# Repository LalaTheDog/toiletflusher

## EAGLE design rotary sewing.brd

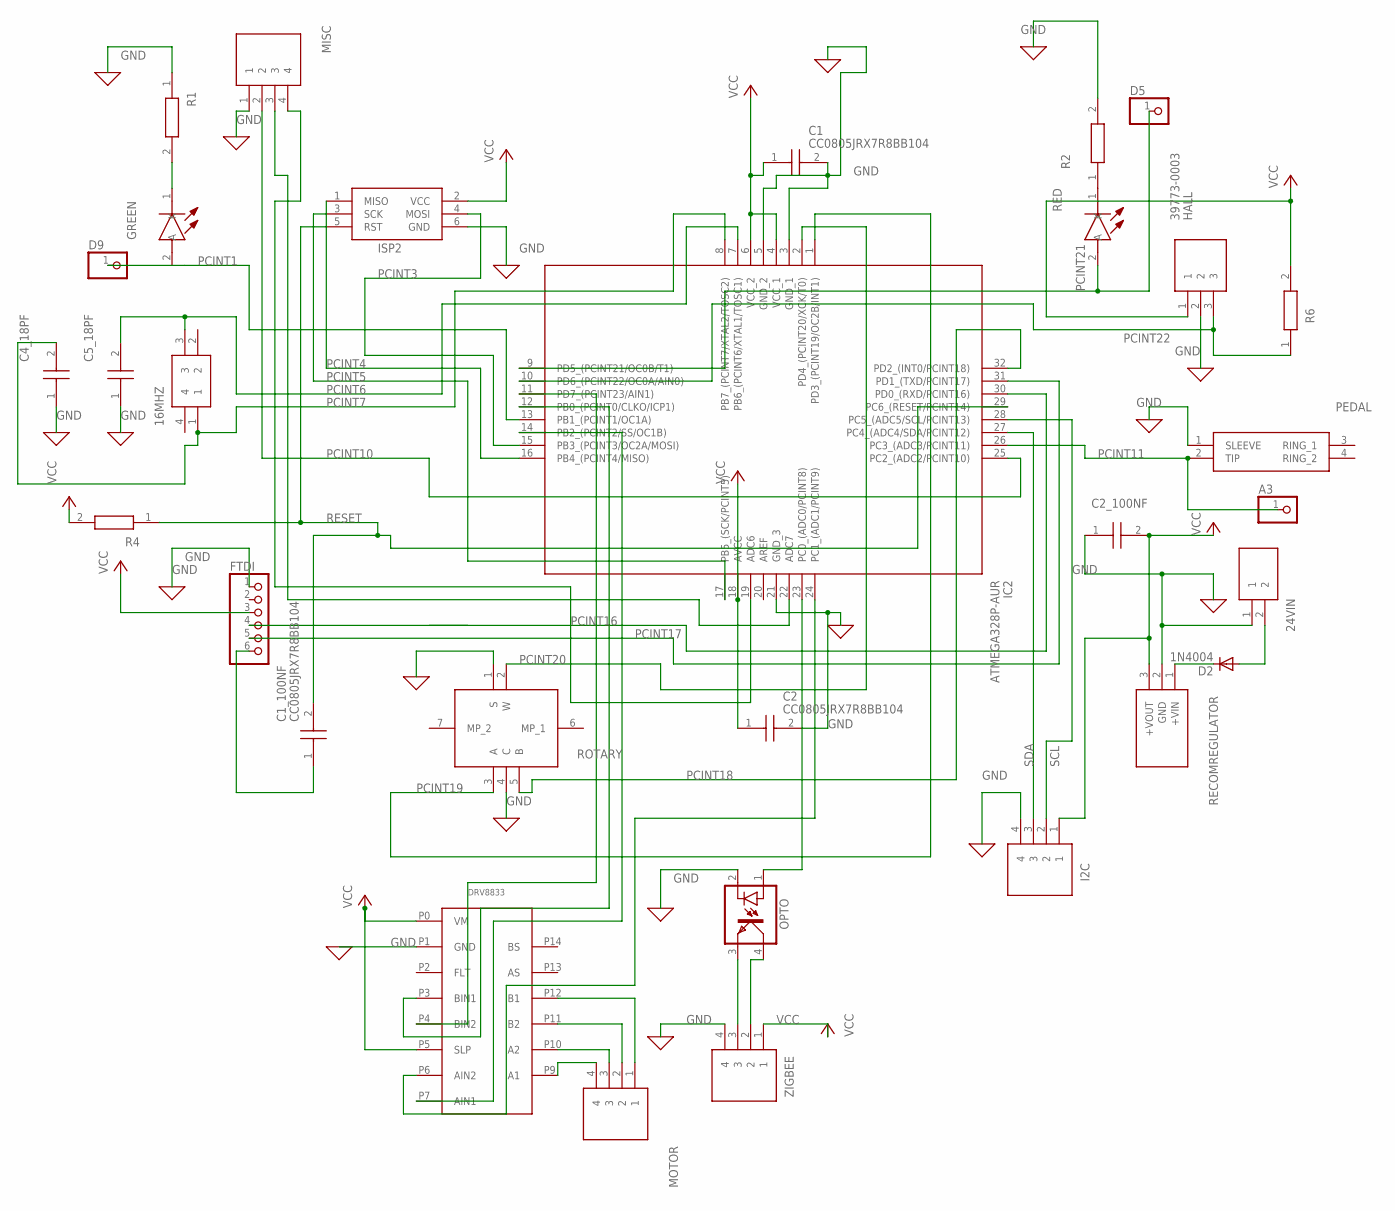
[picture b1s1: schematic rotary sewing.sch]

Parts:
16MHZ: 403C11E16M00000; 403C1XA32M00000
24VIN: 39773-0002; SHDR2W110P0X254_1X2_554X650X10
A3: PINHD-1X1; 1X01
C1, C1_100NF, C2, C2_100NF: CC0805JRX7R8BB104; CAPC2012X135N
C4_18PF, C5_18PF: C0805C180J5GACTU; CAPC2012X88N
D2: 1N4004; DO41-10
D5, D9: PINHD-1X1; 1X01
DRV8833: DRV8833
FTDI: PINHD-1X6; 1X06
GREEN: LTST-C171GKT; LEDC2012X90N
HALL: 39773-0003; SHDR3W80P0X254_1X3_808X650X101
I2C: 39773-0004; SHDR4W80P0X254_1X4_1062X650X10
IC2: ATMEGA328P-AUR; QFP80P900X900X120-32N
ISP2: AVRISP-6; AVRISP
MISC: 39773-0004; SHDR4W80P0X254_1X4_1062X650X10
MOTOR: 39773-0004; SHDR4W80P0X254_1X4_1062X650X10
OPTO: PC817; DIL04
PEDAL: SJ2-3574A-SMT-TR; SJ23574ASMTTR
R1, R2: RMC1_10K1001FTP; RESC2012X65N
R4, R6: ERA-6AED103V; RESC2012X60N
RECOMREGULATOR: R-78E3.3-1.0
RED: LTST-C171KRKT; LEDM2012X90N
ROTARY: PEC11L-4220F-S0015; PEC11L4220FS0015
ZIGBEE: 39773-0004; SHDR4W80P0X254_1X4_1062X650X10

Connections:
GND: 24VIN.1, C1.2, C2.2, C2_100NF.1, C4_18PF.1, C5_18PF.1, DRV8833.P1 (GND), FTDI.1, HALL.2, I2C.4, IC2.3 (GND_1), IC2.5 (GND_2), IC2.21 (GND_3), ISP2.6 (GND), MISC.1, OPTO.2 (C), PEDAL.1 (SLEEVE), R1.1, R2.2, RECOMREGULATOR.2 (GND), ROTARY.1 (S), ROTARY.4 (C), ZIGBEE.4
unnamed: OPTO.3 (EMIT), ZIGBEE.3
unnamed: IC2.23 (PC0_(ADC0/PCINT8)), OPTO.1 (A)
unnamed: OPTO.4 (COL), ZIGBEE.2
unnamed: 24VIN.2, D2.A
unnamed: R2.1, RED.1 (K)
unnamed: GREEN.1 (K), R1.2
unnamed: DRV8833.P9 (A1), MOTOR.4
unnamed: DRV8833.P10 (A2), MOTOR.3
unnamed: DRV8833.P11 (B2), MOTOR.2
unnamed: DRV8833.P12 (B1), MOTOR.1
unnamed: C1_100NF.1, FTDI.6
unnamed: DRV8833.P4 (BIN2), IC2.11 (PD7_(PCINT23/AIN1))
unnamed: D2.C, RECOMREGULATOR.1 (+VIN)
unnamed: DRV8833.P3 (BIN1), IC2.12 (PB0_(PCINT0/CLKO/ICP1))
unnamed: DRV8833.P7 (AIN1), IC2.14 (PB2_(PCINT2/SS/OC1B))
unnamed: DRV8833.P6 (AIN2), IC2.24 (PC1_(ADC1/PCINT9))
unnamed: IC2.22 (ADC7), MISC.3
unnamed: IC2.19 (ADC6), MISC.4
PCINT1: D9.1, GREEN.2 (A), IC2.13 (PB1_(PCINT1/OC1A))
PCINT3: IC2.15 (PB3_(PCINT3/OC2A/MOSI)), ISP2.4 (MOSI)
PCINT4: IC2.16 (PB4_(PCINT4/MISO)), ISP2.1 (MISO)
PCINT5: IC2.17 (PB5_(SCK/PCINT5)), ISP2.3 (SCK)
PCINT6: 16MHZ.3, C5_18PF.2, IC2.7 (PB6_(PCINT6/XTAL1/TOSC1))
PCINT7: 16MHZ.1, C4_18PF.2, IC2.8 (PB7_(PCINT7/XTAL2/TOSC2))
PCINT10: IC2.25 (PC2_(ADC2/PCINT10)), MISC.2
PCINT11: A3.1, IC2.26 (PC3_(ADC3/PCINT11)), PEDAL.2 (TIP)
PCINT16: FTDI.4, IC2.30 (PD0_(RXD/PCINT16))
PCINT17: FTDI.5, IC2.31 (PD1_(TXD/PCINT17))
PCINT18: IC2.32 (PD2_(INT0/PCINT18)), ROTARY.5 (B)
PCINT19: IC2.1 (PD3_(PCINT19/OC2B/INT1)), ROTARY.3 (A)
PCINT20: IC2.2 (PD4_(PCINT20/XCK/T0)), ROTARY.2 (W)
PCINT21: D5.1, IC2.9 (PD5_(PCINT21/OC0B/T1)), RED.2 (A)
PCINT22: HALL.3, IC2.10 (PD6_(PCINT22/OC0A/AIN0)), R6.1
RESET: C1_100NF.2, IC2.29 (PC6_(RESET/PCINT14)), ISP2.5 (RST), R4.1
SCL: I2C.2, IC2.28 (PC5_(ADC5/SCL/PCINT13))
SDA: I2C.3, IC2.27 (PC4_(ADC4/SDA/PCINT12))
VCC: C1.1, C2.1, C2_100NF.2, DRV8833.P0 (VM), DRV8833.P5 (SLP), FTDI.3, HALL.1, I2C.1, IC2.4 (VCC_1), IC2.6 (VCC_2), IC2.18 (AVCC), ISP2.2 (VCC), R4.2, R6.2, RECOMREGULATOR.3 (+VOUT), ZIGBEE.1

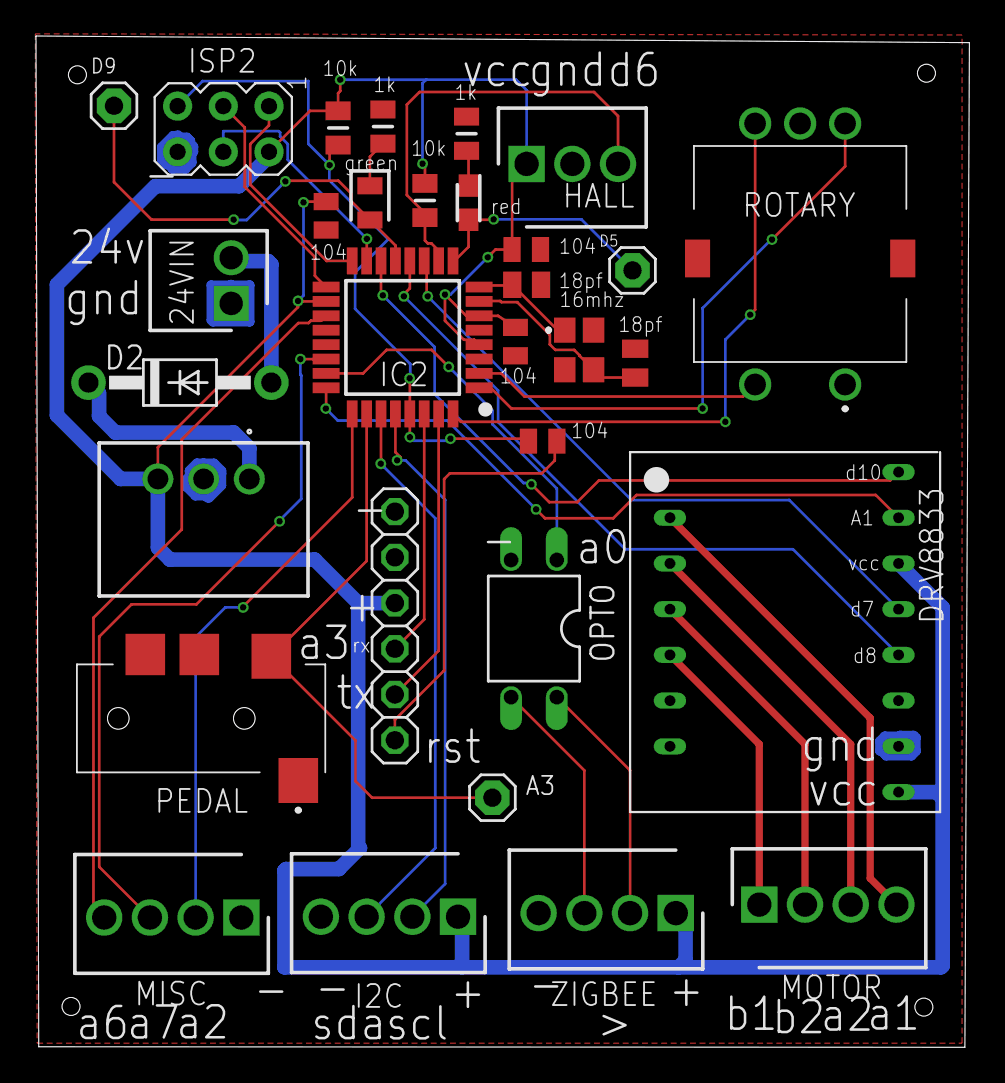
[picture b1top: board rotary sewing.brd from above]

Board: 2 copper layers, 51.9 x 56.2 mm, 31 parts (0 on the bottom side), 38 nets.
